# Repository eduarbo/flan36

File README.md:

# Flan36

**36 keys. Original design. Your keycaps, your frames.**

**[Explore and customize in 3D →](https://eduarbo.github.io/flan36/)** · **[Parts and buying links →](docs/parts.md)** · **[Edit in FreeCAD →](docs/freecad.md)**

*RevI: key-aligned local curves, four interchangeable cases, optional exposed display stack, magnetic frames and a floor-mounted cell in either battery size. Physical fit untested.*

**[Themes and print kits](docs/themes-printing.md)** — Twenty-eight coordinated themes, personal keycap palettes, linked rim/frame colors and selected STL/3MF parts.

**[Lower, level stack](docs/level-stack.md)** — The frame and removable switch-covering shell reach 13.59 mm; the glass sits 0.20 mm below them. Connector fit remains unqualified.

**[Case variants](docs/cases.md)** — Level, Solid, Color rim and Terrace; actual meshes in the explorer.

Flan36 is a low-profile wireless split keyboard in development by [Eduardo Ruiz](https://github.com/eduarbo). Its original CAD is designed by Eduardo, with five columns and three thumb keys per half.

- **KLP Lamé choices:** all 38 Choc-stem variants catalogued; 28 qualify in at least one position. The viewer checks complete combinations and exports a configuration for FreeCAD.
- **Magnetic frames:** Talavera (default), Game Boy, SNES, 2000s Phone, iPod and Hanafuda. Up to four solid colors in flush inlays, with matching rim and key palettes.
- **Keycap colors:** paint all keys, rows, columns or individual keys; save and share your own palettes.
- **Free tools:** KiCad for electronics, FreeCAD for the case, StepUp for exchange. Editable source, STEP/STL, offline viewer and GLB included.
- **Intended hardware:** Choc v1 hot-swap, two nice!nano controllers and two nice!view displays. One display remains the fallback.

**Status: routed prototype; physical qualification pending.** Both PCBs pass DRC, schematic parity and ERC with no unconnected items. Three [ZMK firmware builds](docs/firmware.md) cover two displays or a left-only display. [Prototype fabrication files and verification](docs/electronics.md) are included. Exact connectors, printed retention, BLE, charging and measured power still need hardware tests.

**[Keycaps and frames](docs/customize.md) · [Design](docs/design.md) · [Build](docs/build.md) · [CAD files](docs/cad.md) · [Progress](docs/progress.md)**

[Piantor by beekeeb](https://github.com/beekeeb/piantor) inspired the number of keys. The viewer uses [KLP Lamé by braindefender](https://github.com/braindefender/KLP-Lame-Keycaps). [Credits and licenses](ATTRIBUTION.md). [Contributing](CONTRIBUTING.md).

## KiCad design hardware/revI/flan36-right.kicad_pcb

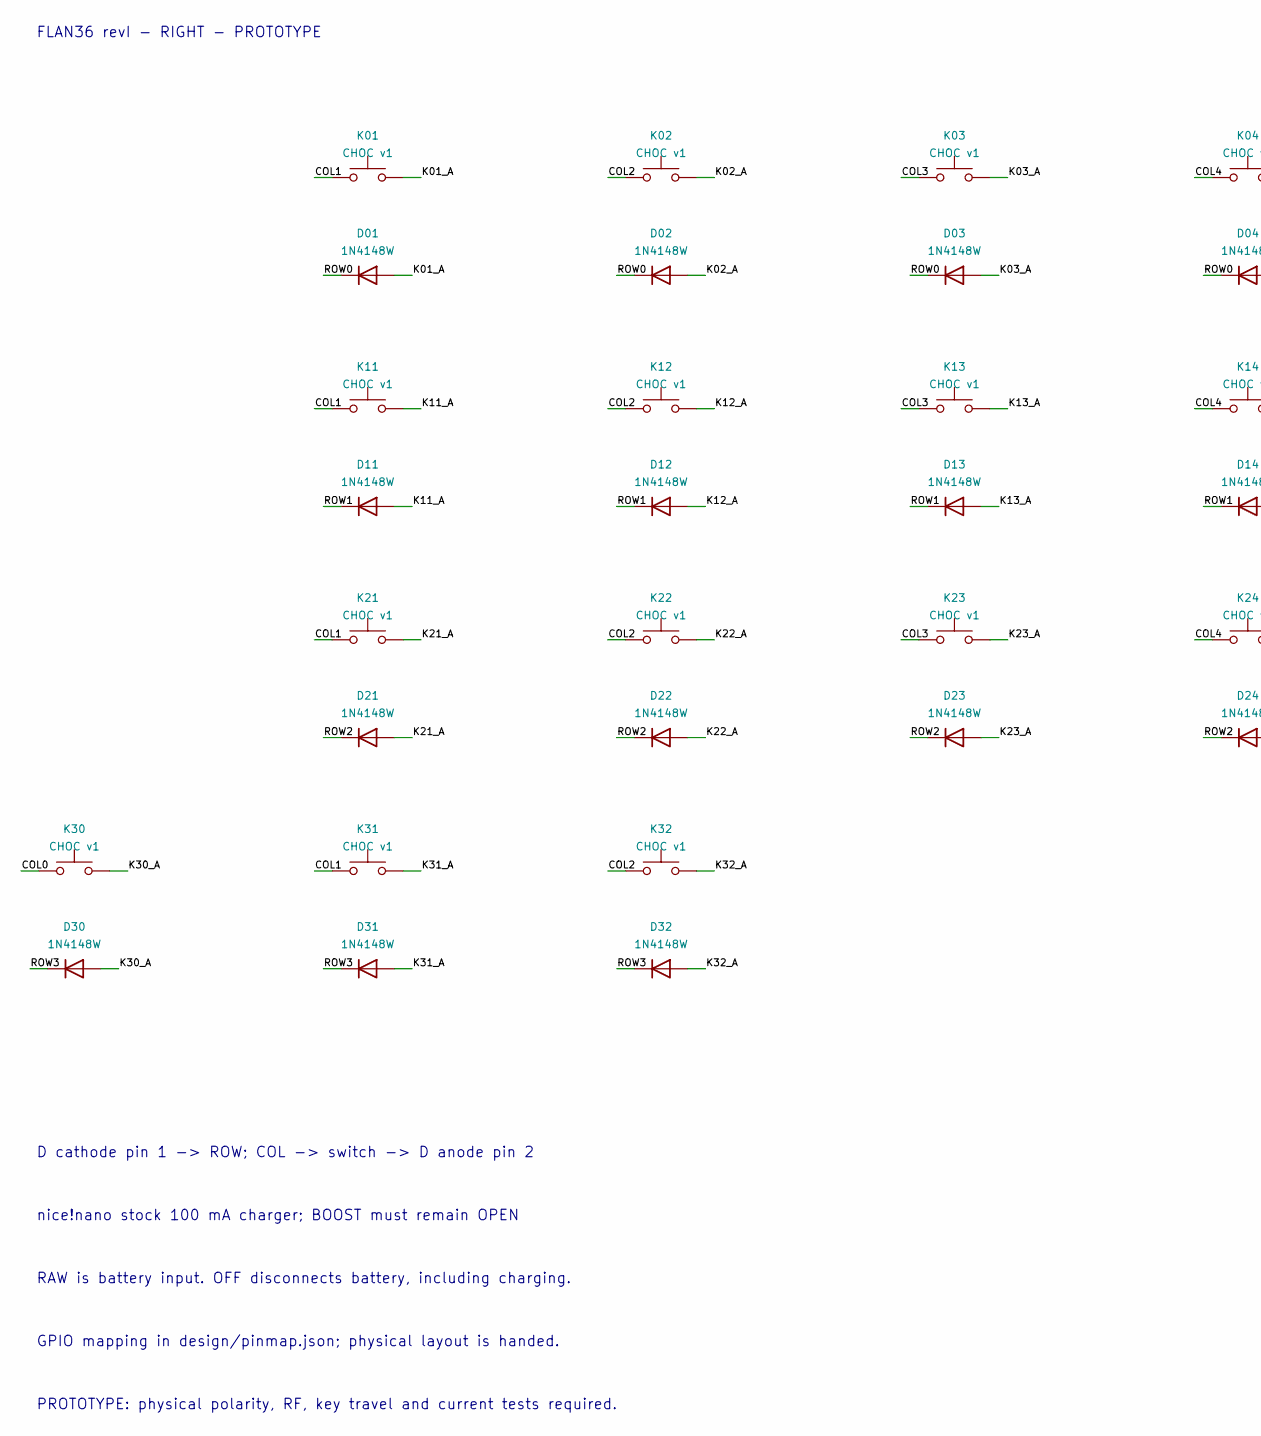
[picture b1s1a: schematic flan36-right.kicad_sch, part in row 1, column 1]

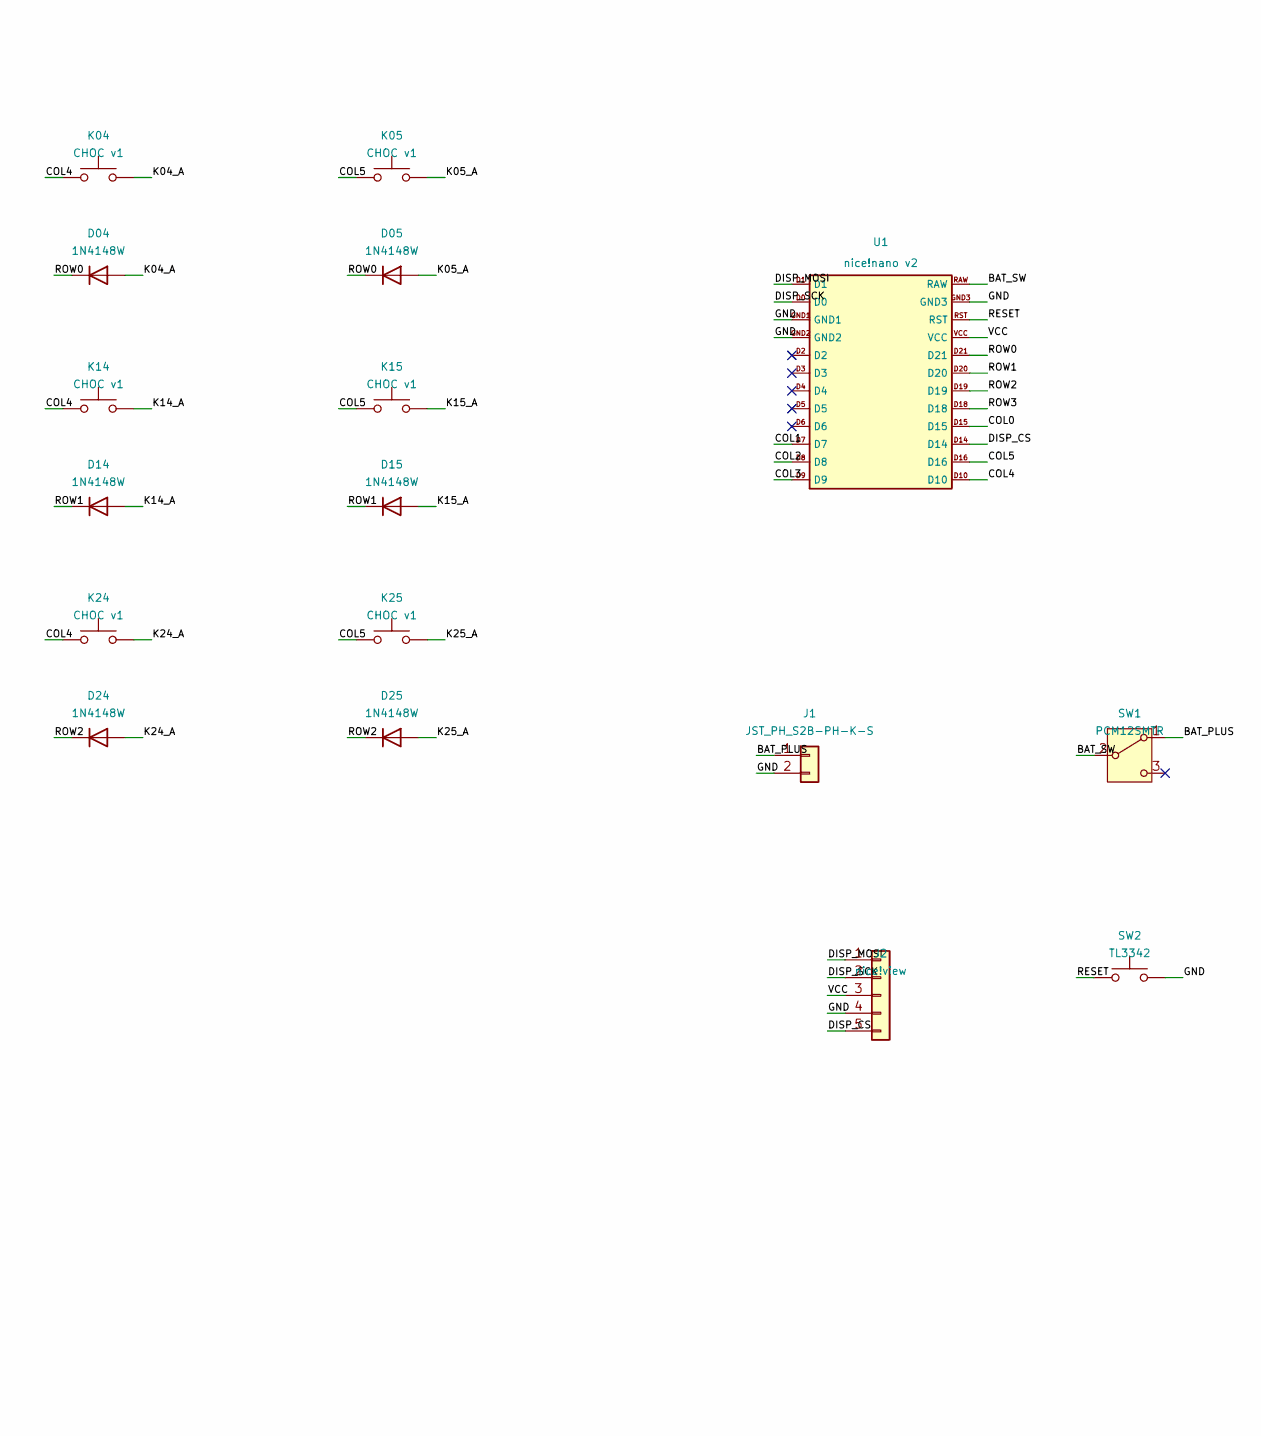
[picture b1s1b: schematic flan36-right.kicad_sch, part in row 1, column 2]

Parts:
D01, D02, D03, D04, D05, D11, D12, D13, D14, D15, D21, D22, D23, D24, D25, D30, D31, D32: 1N4148W; D_SOD-123
J1: JST_PH_S2B-PH-K-S; JST_PH_S2B-PH-K_1x02_P2.00mm_Horizontal
J2: nice!view; nice_view_5pin
K01, K02, K03, K04, K05, K11, K12, K13, K14, K15, K21, K22, K23, K24, K25, K30, K31, K32: CHOC v1; Kailh_socket_PG1350_optional
SW1: PCM12SMTR; SW_SPDT_PCM12
SW2: TL3342; SW_SPST_TL3342
U1: nice!nano v2; nice_nano_v2_standard_edge

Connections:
/BAT_PLUS: J1.1, SW1.1 (A)
/BAT_SW: SW1.2 (B), U1.RAW
/COL0: K30.1, U1.D15
/COL1: K01.1, K11.1, K21.1, K31.1, U1.D7
/COL2: K02.1, K12.1, K22.1, K32.1, U1.D8
/COL3: K03.1, K13.1, K23.1, U1.D9
/COL4: K04.1, K14.1, K24.1, U1.D10
/COL5: K05.1, K15.1, K25.1, U1.D16
/DISP_CS: J2.5, U1.D14
/DISP_MOSI: J2.1, U1.D1
/DISP_SCK: J2.2, U1.D0
/GND: J1.2, J2.4, SW2.2, U1.GND1, U1.GND2, U1.GND3
/K01_A: D01.2 (A), K01.2
/K02_A: D02.2 (A), K02.2
/K03_A: D03.2 (A), K03.2
/K04_A: D04.2 (A), K04.2
/K05_A: D05.2 (A), K05.2
/K11_A: D11.2 (A), K11.2
/K12_A: D12.2 (A), K12.2
/K13_A: D13.2 (A), K13.2
/K14_A: D14.2 (A), K14.2
/K15_A: D15.2 (A), K15.2
/K21_A: D21.2 (A), K21.2
/K22_A: D22.2 (A), K22.2
/K23_A: D23.2 (A), K23.2
/K24_A: D24.2 (A), K24.2
/K25_A: D25.2 (A), K25.2
/K30_A: D30.2 (A), K30.2
/K31_A: D31.2 (A), K31.2
/K32_A: D32.2 (A), K32.2
/RESET: SW2.1, U1.RST
/ROW0: D01.1 (K), D02.1 (K), D03.1 (K), D04.1 (K), D05.1 (K), U1.D21
/ROW1: D11.1 (K), D12.1 (K), D13.1 (K), D14.1 (K), D15.1 (K), U1.D20
/ROW2: D21.1 (K), D22.1 (K), D23.1 (K), D24.1 (K), D25.1 (K), U1.D19
/ROW3: D30.1 (K), D31.1 (K), D32.1 (K), U1.D18
/VCC: J2.3, U1.VCC

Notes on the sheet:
FLAN36 revI - RIGHT - PROTOTYPE
D cathode pin 1 -> ROW; COL -> switch -> D anode pin 2
nice!nano stock 100 mA charger; BOOST must remain OPEN
RAW is battery input. OFF disconnects battery, including charging.
GPIO mapping in design/pinmap.json; physical layout is handed.
PROTOTYPE: physical polarity, RF, key travel and current tests required.

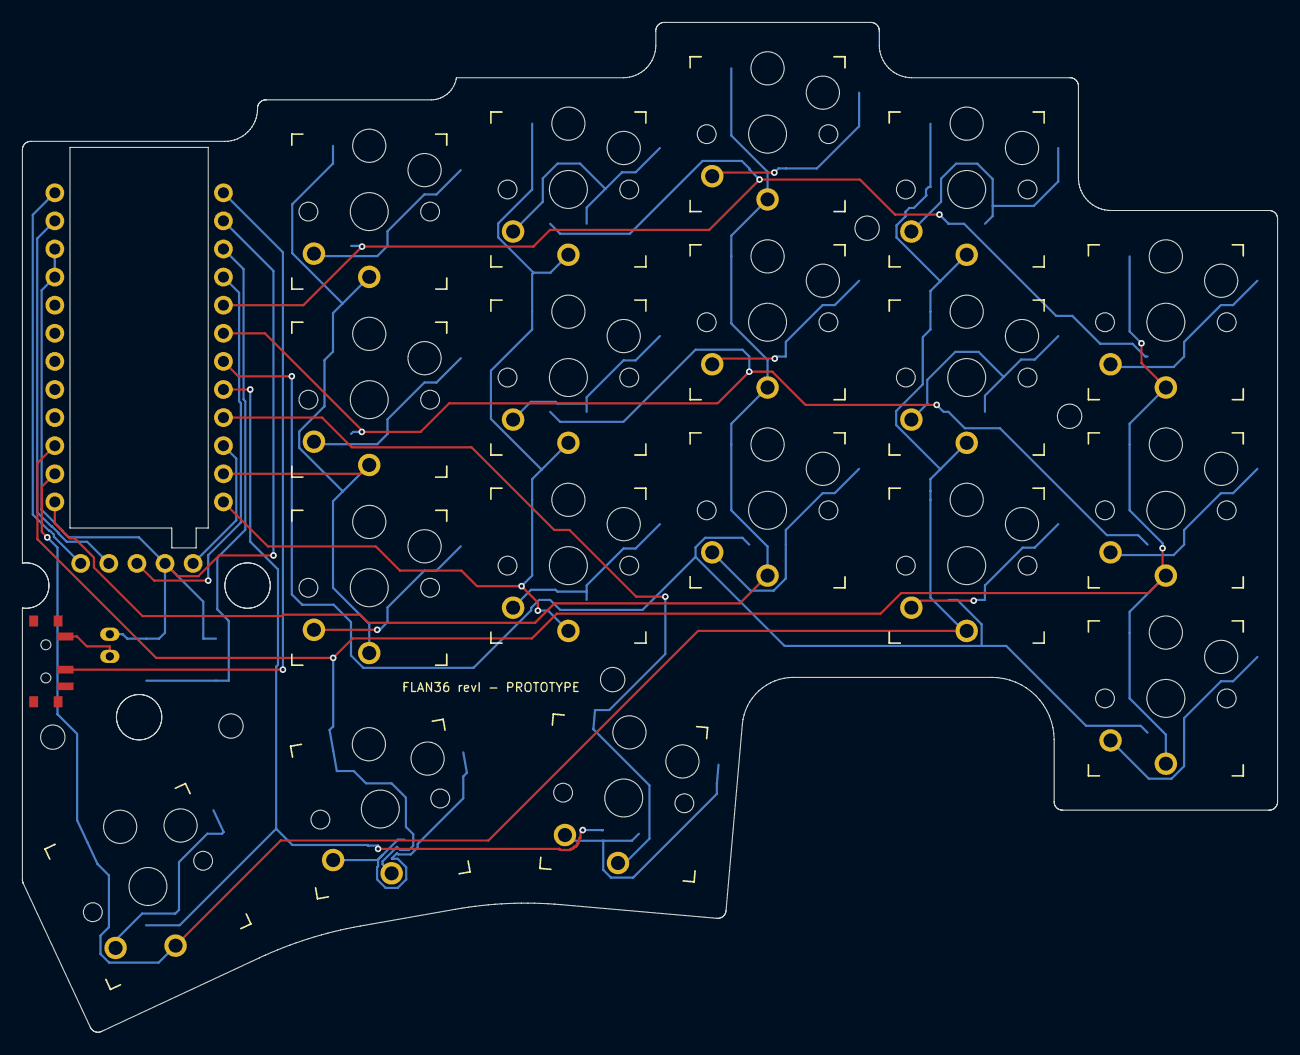
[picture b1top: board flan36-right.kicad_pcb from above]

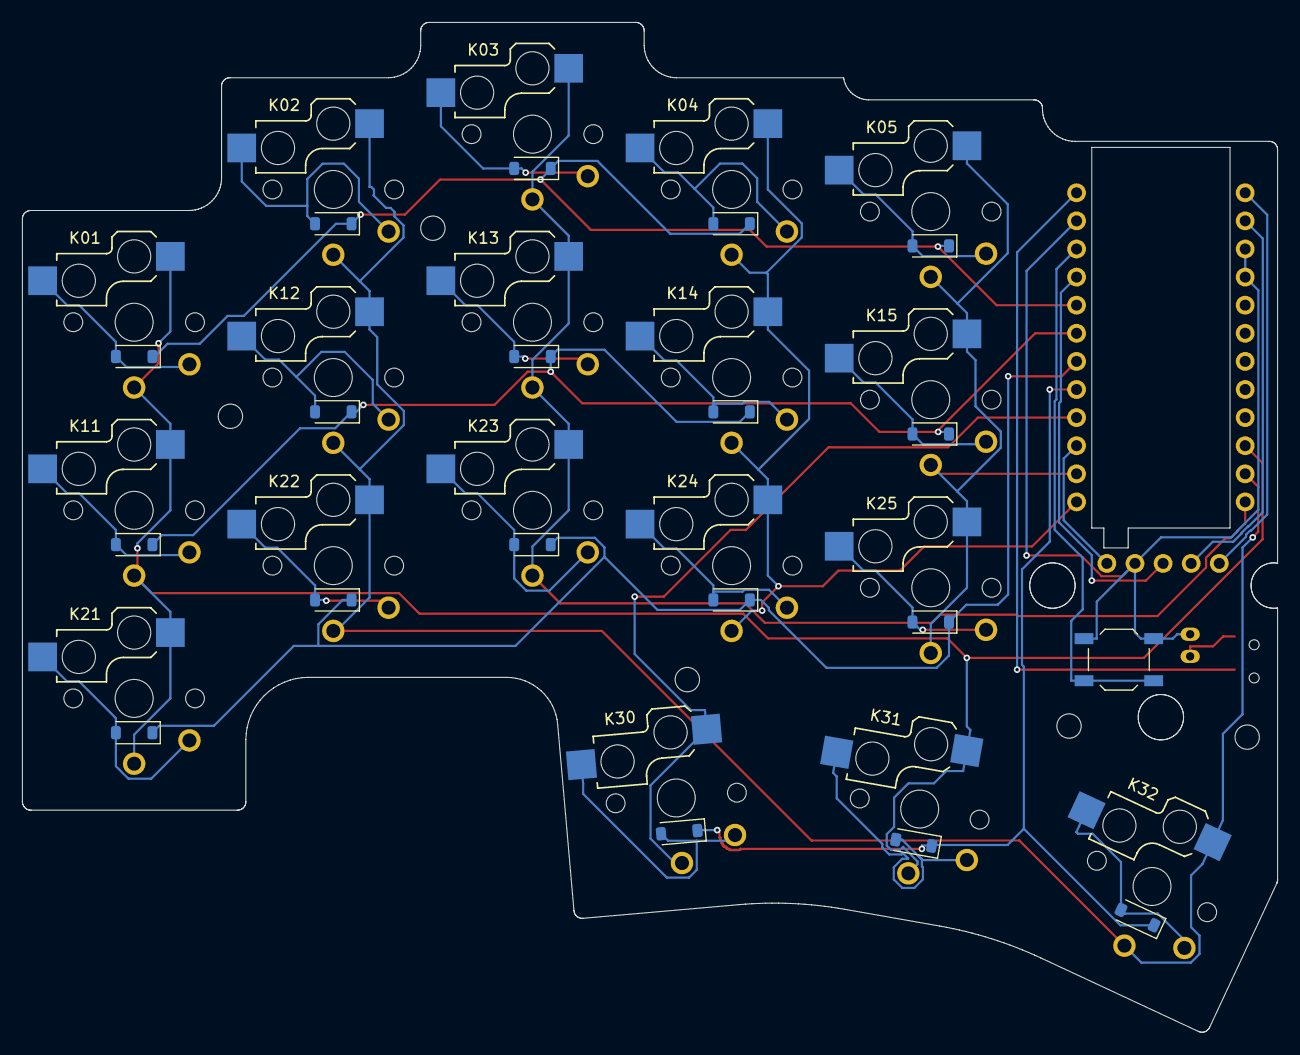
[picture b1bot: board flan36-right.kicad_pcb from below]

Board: 2 copper layers, 113.4 x 91.3 mm, 46 parts (19 on the bottom side), 36 nets.

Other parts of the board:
H1, H2, H3, H4, H5: MountingHole_2.2mm_M2

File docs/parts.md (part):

# Parts and buying guide

**One complete 36-key split. Quantities cover both halves.**

This is a planning BOM for the revI mechanical study and PCB outline. **It is not a verified build kit:** the PCBs are routed and digitally checked, but exact connectors, magnetic retention and printed threads still need physical tests. Store links identify actual products; they do not certify interchangeability.

[Custom PCBs](electronics.md) · [Typeractive shopping list](#typeractive-shopping-list) · [Controllers](#controllers) · [Displays](#displays) · [Switches](#switches-and-hot-swap) · [Battery](#battery) · [Connectors](#removable-connectors) · [Small parts](#small-electrical-parts) · [Printed parts](#printed-parts)

**Custom PCBs: 1 left + 1 right**, two layers, 1.6 mm FR4, nominal 1 oz copper. Use the [matched prototype fabrication packages](electronics.md), after checking the exact connector and battery fit. The supplied pin maps differ between halves; neither board is interchangeable with Piantor or the historical placement studies.

## Typeractive shopping list

| Item | Quantity / store selection | Fit status |
|---|---|---|
| [nice!nano v2](https://typeractive.xyz/products/nice-nano) | **2 units** | Selected controller; final socket height pending |
| [nice!view](https://typeractive.xyz/products/nice-view) | **2 units**, or 1 for the fallback | Selected display; included connector does not establish stack fit |
| [Choc v1 switches](https://typeractive.xyz/products/choc-switches) | **4 packs of 10**; Pro Red baseline | 36 required, 4 spares |
| [Kailh hot-swap sockets](https://typeractive.xyz/products/hotswap-sockets) | **4 packs of 10; select Choc** | Do not select MX |
| [1N4148W SMD diodes](https://typeractive.xyz/products/smd-diodes) | **4 packs of 10** | SOD-123 family; verify supplied marking/footprint |
| [Machine sockets and pins](https://typeractive.xyz/products/machine-sockets-and-pins) | **2 kits** | Store uses Mill-Max **310**, study references **315**; substitution needs height/pin check |
| [EZ-Solder sockets/headers](https://typeractive.xyz/products/ez-machine-sockets-and-headers) | **2 kits**, instead of the preceding kits | Easier header handling; taller, not qualified in this stack |
| [5-pin sockets](https://typeractive.xyz/products/5-pin-sockets) | Optional **1 pack of 2** | Extras; nice!view includes sockets/pins. Stock alternative for the previous taller stack; the current prototype uses the Samtec candidate below |
| [110 mAh battery](https://typeractive.xyz/products/lithium-battery-110mah) | **2**, connector variant to resolve | Supported nominal envelope in the shared 12.5 mm aperture; physical pack fit pending |
| [Battery jack](https://typeractive.xyz/products/battery-jack) | **1 pack of 2** | JST S2B-PH-K-S side-entry reference; 2 mm nominal footprint |
| [Power switch](https://typeractive.xyz/products/power-switch) | **1 pack of 2** | Alps part differs from the C&K reference; footprint change/check required |
| [Reset button](https://typeractive.xyz/products/reset-button) | **1 pack of 2** | Panasonic part differs from the E-Switch reference; not a drop-in approval |

The selected Adafruit battery, custom PCB and printed parts are outside this store list. Prices, stock and shipping eligibility can change; check the selected variant and delivery destination at checkout. No purchases have been made.

## Controllers

<a href="https://typeractive.xyz/products/nice-nano"><img src="https://cdn.shopify.com/s/files/1/0618/5674/3655/products/ne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" width="210" alt="nice!nano v2.0 — supplier product photo"></a>

**2 × nice!nano v2.** nRF52840 wireless controllers with USB-C and battery charging. They provide the intended BLE link between halves and to the host.

**Technical reference:** [v2 pinout and schematic](https://nicekeyboards.com/docs/nice-nano/pinout-schematic/). **Full documentation:** [nice!nano](https://nicekeyboards.com/docs/nice-nano/). **Buy:** [Typeractive](https://typeractive.xyz/products/nice-nano).

Alternatives: clones require independent pinout, charger and idle-current checks. XIAO or other controller formats require a PCB and mounting redesign. No alternative is approved as a direct replacement.

## Displays

<a href="https://typeractive.xyz/products/nice-view"><img src="https://cdn.shopify.com/s/files/1/0618/5674/3655/products/ni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" width="210" alt="nice!view — supplier product photo"></a>

**2 × nice!view**, with a single left display as the fallback. Reflective memory LCD; selected for low power. Each cover leaves the glass visible and hides the surrounding electronics.

**Technical reference:** [dimensions, pinout and schematic](https://nicekeyboards.com/docs/nice-view/pinout-schematic/). **Full specifications/setup:** [nice!view documentation](https://nicekeyboards.com/docs/nice-view/). **Buy:** [Typeractive](https://typeractive.xyz/products/nice-view).

A separate board PDF datasheet is not linked by the manufacturer; its dimensioned drawings and schematic are the authoritative board references. OLED offers dark-room visibility at a power cost. E-paper needs a different mount and firmware. Neither fits this design as a drop-in alternative.

## Switches and hot-swap

<a href="https://typeractive.xyz/products/choc-switches"><img src="https://cdn.shopify.com/s/files/1/0618/5674/3655/products/ch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" width="210" alt="Kailh Choc v1 Low Profile Switches — supplier product photo"></a>

**36 × Kailh Choc v1; 40 provides spares.** Pro Red 35 gf is the baseline; Pink 20 gf is lighter, Red 50 gf firmer, Brown tactile and White clicky. Silent Ambients are another Choc-family option to measure before adopting.

**Technical information:** [Kailh PG1350 family](https://www.kailhswitch.com/info/kailh-kl-switches-pg1350-se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 **Variant specifications and purchase:** [Typeractive Choc v1](https://typeractive.xyz/products/choc-switches). **Silent alternative:** [LowproKB Ambients](https://lowprokb.ca/products/ambients-silent-choc-switches).

An exact Pro Red manufacturer PDF has not been verified here; the family page is not a substitute for a variant-specific drawing. Choc v2/MX-stem switches are outside this build.

<a href="https://typeractive.xyz/products/hotswap-sockets"><img src="https://cdn.shopify.com/s/files/1/0618/5674/3655/products/ho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" width="210" alt="Kailh Hotswap Sockets — supplier product photo"></a>

**36 × Kailh CPG135001S30 Choc sockets; 40 provides spares.**

**Datasheet/drawing:** [Kailh CPG135001S30 PDF](https://www.kailhswitch.com/Content/upload/pdf/202115927/CPG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 **Info and purchase:** [Typeractive — select Choc](https://typeractive.xyz/products/hotswap-sockets). The product photo includes both families; the **MX** variant is incompatible.

All 36 sockets are represented in the nominal assembly and registered to their PCB mounting bores and solder-contact planes. The case includes a local H3 support relief, measured at **0.25 mm nominal clearance** from thumb socket K30 on both halves. [Component geometry and clearance evidence](../components/README.md) do not qualify a purchased variant, solder thickness or printed fit.

## Battery

<a href="https://www.adafruit.com/product/1570"><img src="https://cdn-shop.adafruit.com/145x109/1570-00.jpg" width="210" alt="Adafruit 1570 battery — supplier product photo"></a>

**CAD reference: 2 × Adafruit 1570, protected 1S LiPo, sold as 100 mAh.** The model uses the product page’s **11.5 × 31 × 3.8 mm** envelope; two continuous nominal 105 mm lead paths include cell-end bends and plug interfaces. Their 0.6 mm insulation diameter and terminal positions remain assumptions.

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
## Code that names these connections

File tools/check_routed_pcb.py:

#!/usr/bin/env python3
"""Read every physical pad and independently check the routed revI boards.
Run with KiCad Python. SPDX-License-Identifier: GPL-3.0-or-later
"""
import argparse
import hashlib
import json
import subprocess
import xml.etree.ElementTree as ET
from decimal import Decimal, InvalidOperation
from pathlib import Path

import pcbnew as p
from check_layout import read_sexpr

ROOT = Path(__file__).resolve().parents[1]
BASELINE = "fe8c7fdc1b13b8eac6383c3315af8e749b1b8d4c"


def geometry(board):
    result = {}
    for fp in board.GetFootprints():
        pads = []
        for q in fp.Pads():
            pads.append((q.m_Uuid.AsString(), q.GetNumber(), q.GetPosition().x, q.GetPosition().y,
                         q.GetOrientationDegrees(), q.GetSize().x, q.GetSize().y,
                         q.GetDrillSize().x, q.GetDrillSize().y, q.GetShape(), q.GetAttribute(),
                         q.GetLayerSet().FmtHex()))
        result[fp.GetReference()] = {"uuid": fp.m_Uuid.AsString(),
            "xy": [fp.GetPosition().x, fp.GetPosition().y], "angle": fp.GetOrientationDegrees(),
            "layer": fp.GetLayer(), "locked": fp.IsLocked(), "symbol": fp.GetPath().AsString(),
            "pads": sorted(pads), "models": [m.m_Filename for m in fp.Models()]}
    return result


def edges(path):
    tree = read_sexpr(path.read_text())
    # KiCad adds missing UUIDs and removes trailing decimal zeroes when saving.
    # Compare exact decimal geometry, independent of those serialization changes.
    def canonical(node):
        if isinstance(node, list):
            return tuple(canonical(c) for c in node if not (isinstance(c, list) and c[0] == "uuid"))
        try:
            return str(Decimal(node).normalize())
        except InvalidOperation:
            return node
    return sorted(repr(canonical(n)) for n in tree if isinstance(n, list) and n[0].startswith("gr_")
                  and any(isinstance(c, list) and c[:2] == ["layer", "Edge.Cuts"] for c in n))


def verify(directory, output, cli):
    output.mkdir(parents=True, exist_ok=True)
    result = {"schema": "flan36-routed-pcb-1", "baseline": BASELINE,
              "kicad_version": p.GetBuildVersion(), "physical_acceptance": False, "halves": {}}
    pinmap = json.loads((ROOT / "design/pinmap.json").read_text())["halves"]
    layout = json.loads((ROOT / "design/layout.json").read_text())["halves"]
    for side in ("left", "right"):
        name = f"flan36-{side}"
        board_path = directory / (name + ".kicad_pcb")
        sch_path = board_path.with_suffix(".kicad_sch")
        original = output / (name + "-baseline.kicad_pcb")
        original.write_bytes(subprocess.check_output(["git", "show", f"{BASELINE}:hardware/revI/{name}.kicad_pcb"], cwd=ROOT))
        board = p.LoadBoard(str(board_path)); old = p.LoadBoard(str(original))
        assert geometry(board) == geometry(old), "Component/pad/pose/model mutation"
        assert edges(board_path) == edges(original), "Outline or aperture changed"
        assert board.GetTracks(), "Unrouted study is not accepted"
        assert board.GetCopperLayerCount() == 2
        netfile = output / (name + "-netlist.xml")
        subprocess.run([cli, "sch", "export", "netlist", "--format", "kicadxml", "-o", str(netfile), str(sch_path)], check=True)
        root = ET.parse(netfile).getroot()
        expected = {(node.get("ref"), node.get("pin")): net.get("name")
                    for net in root.findall("./nets/net") for node in net.findall("node")}
        fps = {f.GetReference(): f for f in board.GetFootprints()}
        physical_pads = 0
        for fp in fps.values():
            for pad in fp.Pads():
                physical_pads += 1
                assert pad.GetNetname() == expected.get((fp.GetReference(), pad.GetNumber()), ""), (
                    side, fp.GetReference(), pad.GetNumber(), pad.m_Uuid.AsString())
        for key in layout[side]:
            ref = key["ref"]; diode = "D" + ref[1:]
            assert expected[ref, "1"] == f'/COL{key["col"]}'
            assert expected[ref, "2"] == expected[diode, "2"] == f"/{ref}_A"
            assert expected[diode, "1"] == f'/ROW{key["row"]}'
        pins = {"D0": "DISP_SCK", "D1": "DISP_MOSI", "D14": "DISP_CS", "RAW": "BAT_SW", "VCC": "VCC", "RST": "RESET"}
        pins.update({f"D{x}": f"ROW{i}" for i, x in enumerate(pinmap[side]["rows"])})
        pins.update({f"D{x}": f"COL{i}" for i, x in enumerate(pinmap[side]["cols"])})
        for pad, net in pins.items(): assert expected["U1", pad] == "/"+net
        for i, net in enumerate(("DISP_MOSI", "DISP_SCK", "VCC", "GND", "DISP_CS"), 1):
            assert expected["J2", str(i)] == "/"+net
        for ref, pad, net in [("J1","1","BAT_PLUS"),("J1","2","GND"),("SW1","1","BAT_PLUS"),("SW1","2","BAT_SW"),("SW2","1","RESET"),("SW2","2","GND")]:
            assert expected[ref,pad] == "/"+net
        counts = {}
        for kind, check, source in (("pcb", "drc", board_path), ("sch", "erc", sch_path)):
            report = output / f"{check}-{side}.json"
            command = [cli, kind, check, "--format", "json", "--severity-all", "--exit-code-violations", "-o", str(report)]
            if kind == "pcb": command += ["--schematic-parity", "--all-track-errors"]
            subprocess.run(command + [str(source)], check=True)
            data = json.loads(report.read_text())
            if kind == "pcb":
                assert not data["violations"] and not data["unconnected_items"] and not data["schematic_parity"]
                counts.update(drc_violations=0, unconnected_items=0, schematic_parity=0)
            else:
                assert not any(s["violations"] for s in data["sheets"])
                counts["erc_violations"] = 0
        widths = [p.ToMM(t.GetWidth()) for t in board.GetTracks() if not isinstance(t,p.PCB_VIA)]
        assert min(widths) >= .2 - 1e-7
        result["halves"][side] = {**counts, "components": len(fps), "physical_pads_checked": physical_pads,
            "matrix_keys": 18, "tracks_and_vias": len(board.GetTracks()), "minimum_track_mm": min(widths),
            "poses_pads_models_and_outline_preserved": True,
            "pcb_sha256": hashlib.sha256(board_path.read_bytes()).hexdigest(),
            "schematic_sha256": hashlib.sha256(sch_path.read_bytes()).hexdigest(),
            "rules_sha256": hashlib.sha256(board_path.with_suffix(".kicad_pro").read_bytes()).hexdigest()}
    (ROOT / "validation/revI-routing.json").write_text(json.dumps(result, indent=2)+"\n")
    print("PASS: both boards connected; all physical pads, semantic matrix and unchanged geometry verified")


if __name__ == "__main__":
    ap = argparse.ArgumentParser(description=__doc__)
    ap.add_argument("--directory", type=Path, default=ROOT/"hardware/revI")
    ap.add_argument("--output", type=Path, default=ROOT/"build/routing-validation")
    ap.add_argument("--cli", default="/Applications/KiCad/KiCad.app/Contents/MacOS/kicad-cli")
    a=ap.parse_args(); verify(a.directory.resolve(), a.output.resolve(), a.cli)

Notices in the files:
docs/parts.md:
they are not relicensed under this repository’s license. They need internet access and are not bundled in the offline 3D viewer. Flan36 renders have separate [attribution](../ATTRIBUTION.md).
